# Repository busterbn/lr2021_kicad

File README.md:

# LR2021 868/915 MHz eval module in KiCad

KiCad 10 port of Semtech's LR2021 reference design, the 868/915 MHz evaluation module (e788v01a), converted from the original Altium project.

- `e788v01a/` KiCad project (schematic, board, design rules, symbol and footprint libraries with 3D models)
- `tools/` scripts used for the conversion

Open `e788v01a/LR2021_e788v01a_868_915_eval_module.kicad_pro` in KiCad 10 or newer.

## Verification

- Schematic and PCB connectivity match pin by pin (`tools/check.sh`). The Altium board was used as the reference.
- The board's 107 nets match the Altium PcbDoc, and footprint placement matches Semtech's pick and place file.
- Gerbers plotted from KiCad match Semtech's production Gerbers on all copper, solder mask and paste layers (`tools/gerber_diff.py`). Drill holes match in count and size.

## Notes

- Update PCB from Schematic shows no changes.
- KiCad treats references without a trailing number as unannotated, so 17 Altium designators got a "1" appended (`J7_SWD` is `J7_SWD1`, `868M` is `868M1`, `ANT_HF` is `ANT_HF1`). On the board, their reference fields are hidden and the original names are plain footprint texts at the same place, so the silkscreen is unchanged. If you rename one of these parts, edit that text too.
- The accessories sheet is a sub-sheet of the main sheet. The Altium project was flat, so labels shared by both sheets are global labels.
- `ANT_HF1` and `ANT_LF1` use a 3-pin symbol (1 signal, 2 and 3 GND). The original SMA footprint had pads 1, 2, 2; the second GND pad is now pad 3. The copper is unchanged.
- The Altium logo symbols had a hidden zero-length dummy pin without a pad. It is removed.
- Semtech's Altium design rules are in the `.kicad_pro` board setup, the netclasses and `.kicad_dru`. The RF clearance rules used Altium's auto-generated net names (`NetL*`, `NetC*`, `NetA*`). These nets are in the `RF` netclass.
- 42 vias under U1 and next to the XIAO module are not tented on the bottom side, as in the original.
- DRC still shows warnings that come from the original design: solder mask openings on Q1 that bridge nets, a small VBAT_3V3 copper island on the bottom layer, silkscreen overlaps and a few dangling track stubs.
- ERC shows off-grid warnings (Altium grid) and "power input not driven" errors from Altium pin types.
- `kicad-cli pcb drc --schematic-parity` reports "No corresponding pin" for nets without labels. This looks like a CLI issue.

## Conversion

1. KiCad: File > Import Non-KiCad Project > Altium Project, then save the schematic.
2. `make_hierarchy.py`: turns the two top-level sheets into root sheet plus sub-sheet.
3. `fix_labels.py`, `annotate_power.py`, `fix_pads.py`, `relink.py`, `netmap.py`, `fplib.py`, `export_fps.py`, `rules.py`, `fix_tenting.py`, `fix_refs.py` (then `relink.py`, `netmap.py` and `rules.py` again, since auto-generated net names follow the references), `fix_nopads.py`.
4. KiCad: Update PCB from Schematic, which only adds KiCad 10 footprint metadata and nets for unused pins.
5. After each step, `check.sh` compares schematic and PCB connectivity.

The KiCad Python scripts (`fix_pads.py`, `export_fps.py`, `fix_refs.py`, `fix_nopads.py`) run with KiCad's bundled Python. `fix_tenting.py` and `gerber_diff.py` need `olefile`, `gerbonara`, `pillow` and `numpy`.

## License

The design is Semtech's. Semtech's download contains no license terms, so ask Semtech before you publish or redistribute it. This is not an official Semtech release.

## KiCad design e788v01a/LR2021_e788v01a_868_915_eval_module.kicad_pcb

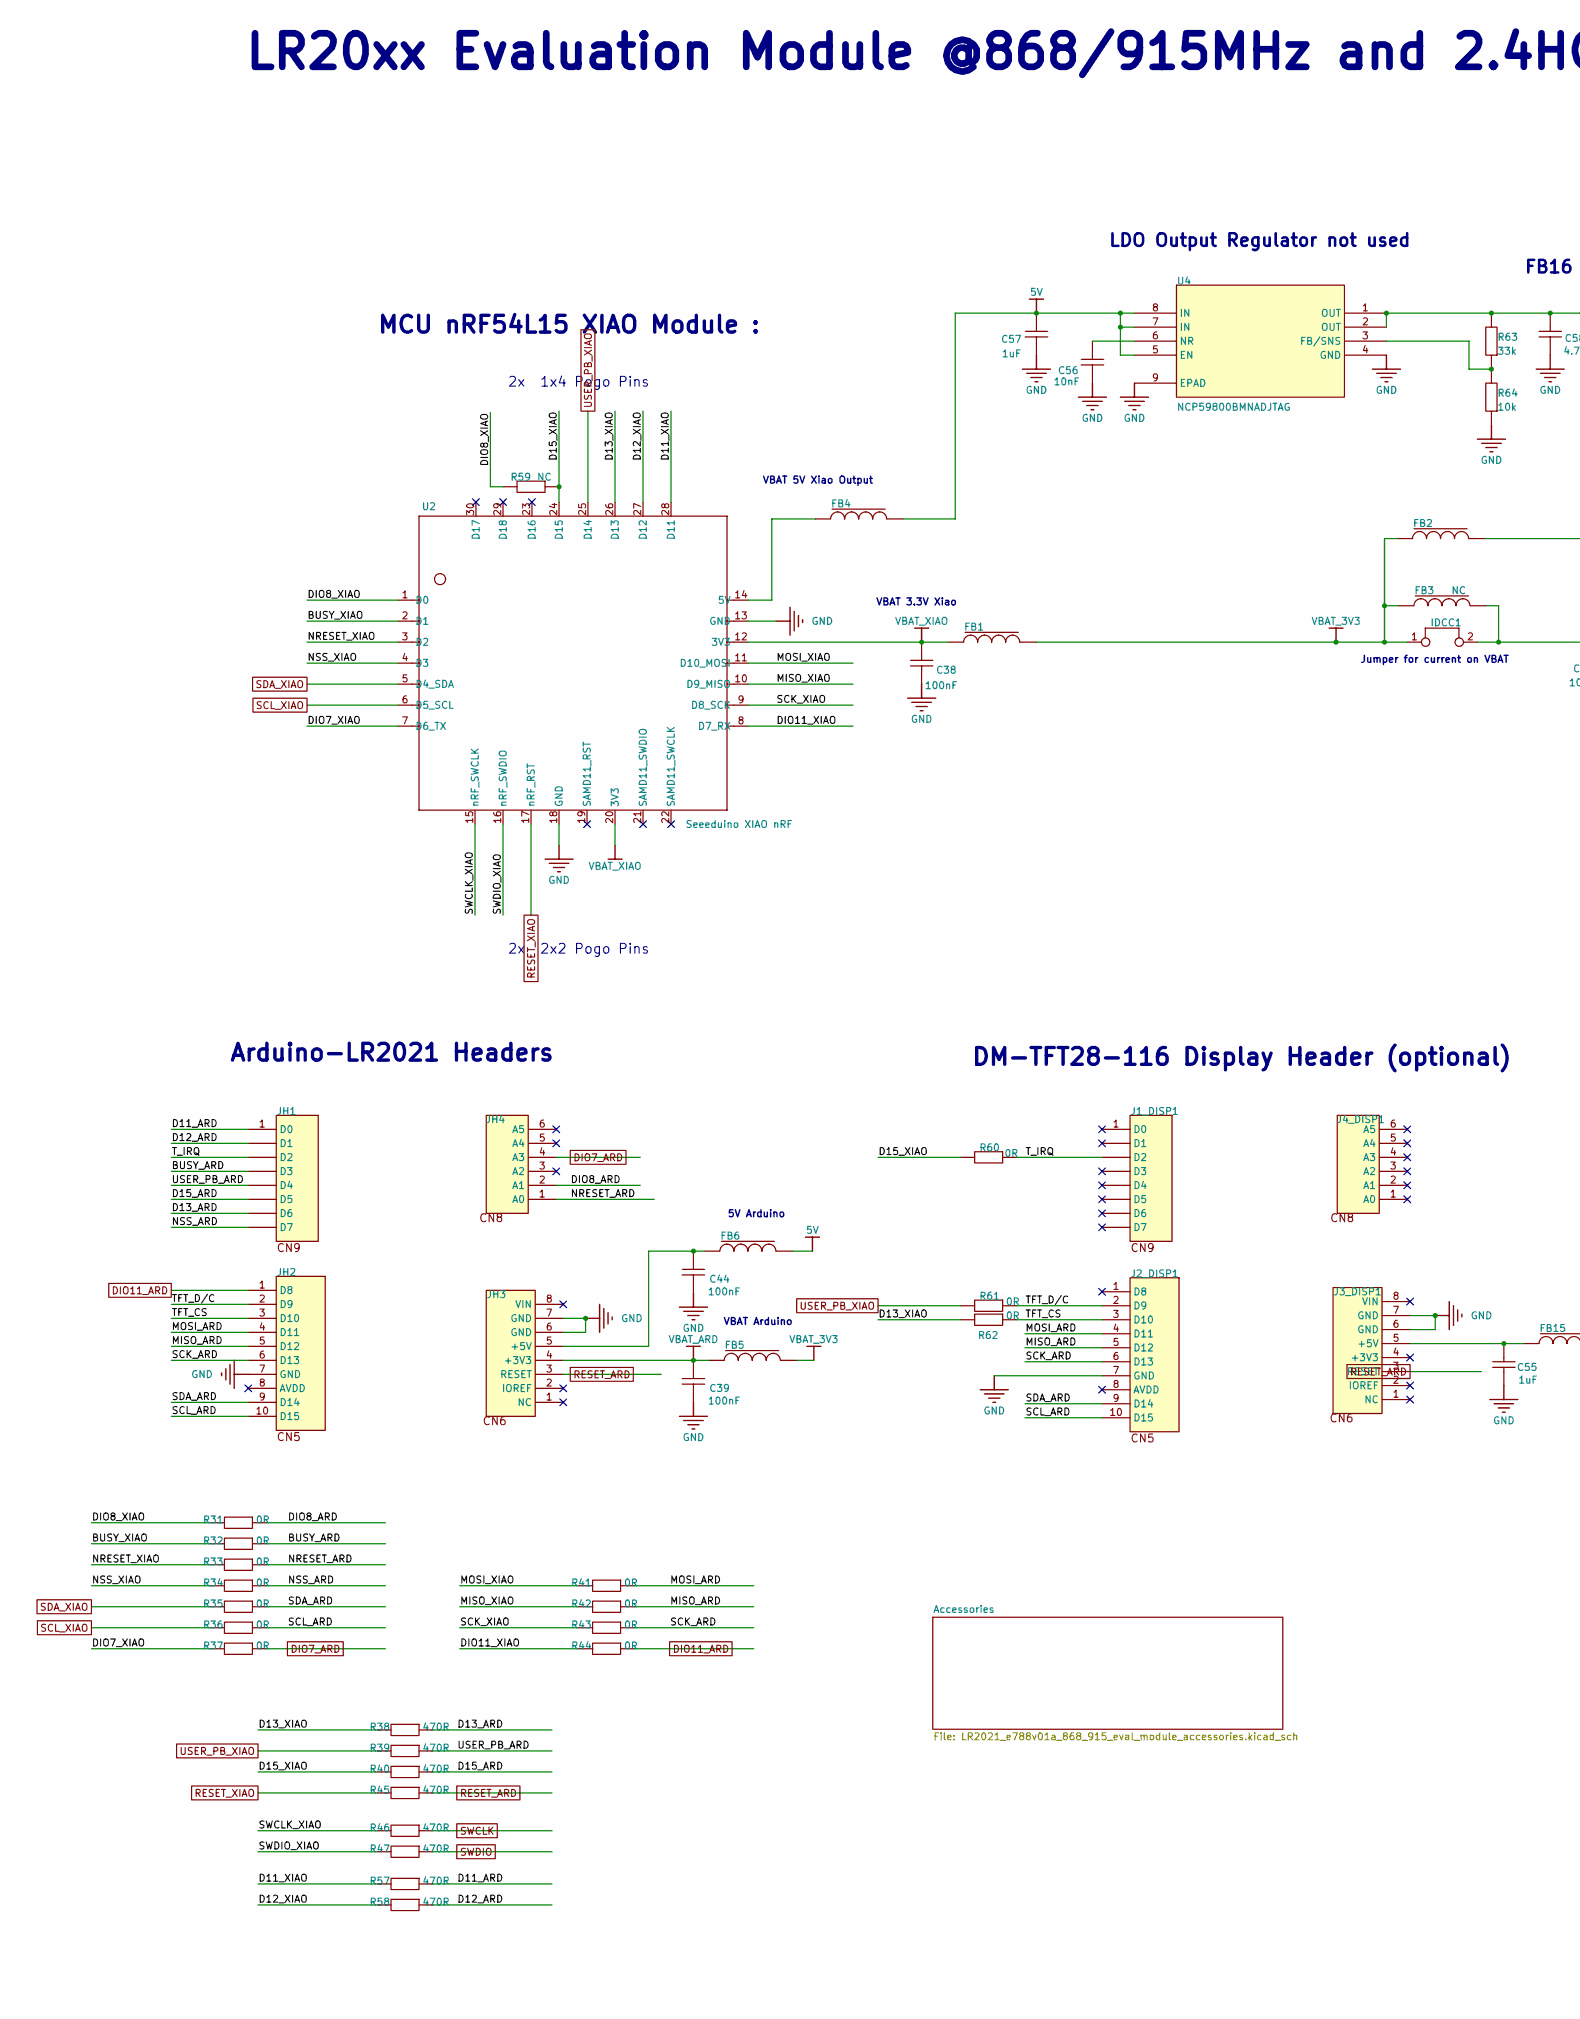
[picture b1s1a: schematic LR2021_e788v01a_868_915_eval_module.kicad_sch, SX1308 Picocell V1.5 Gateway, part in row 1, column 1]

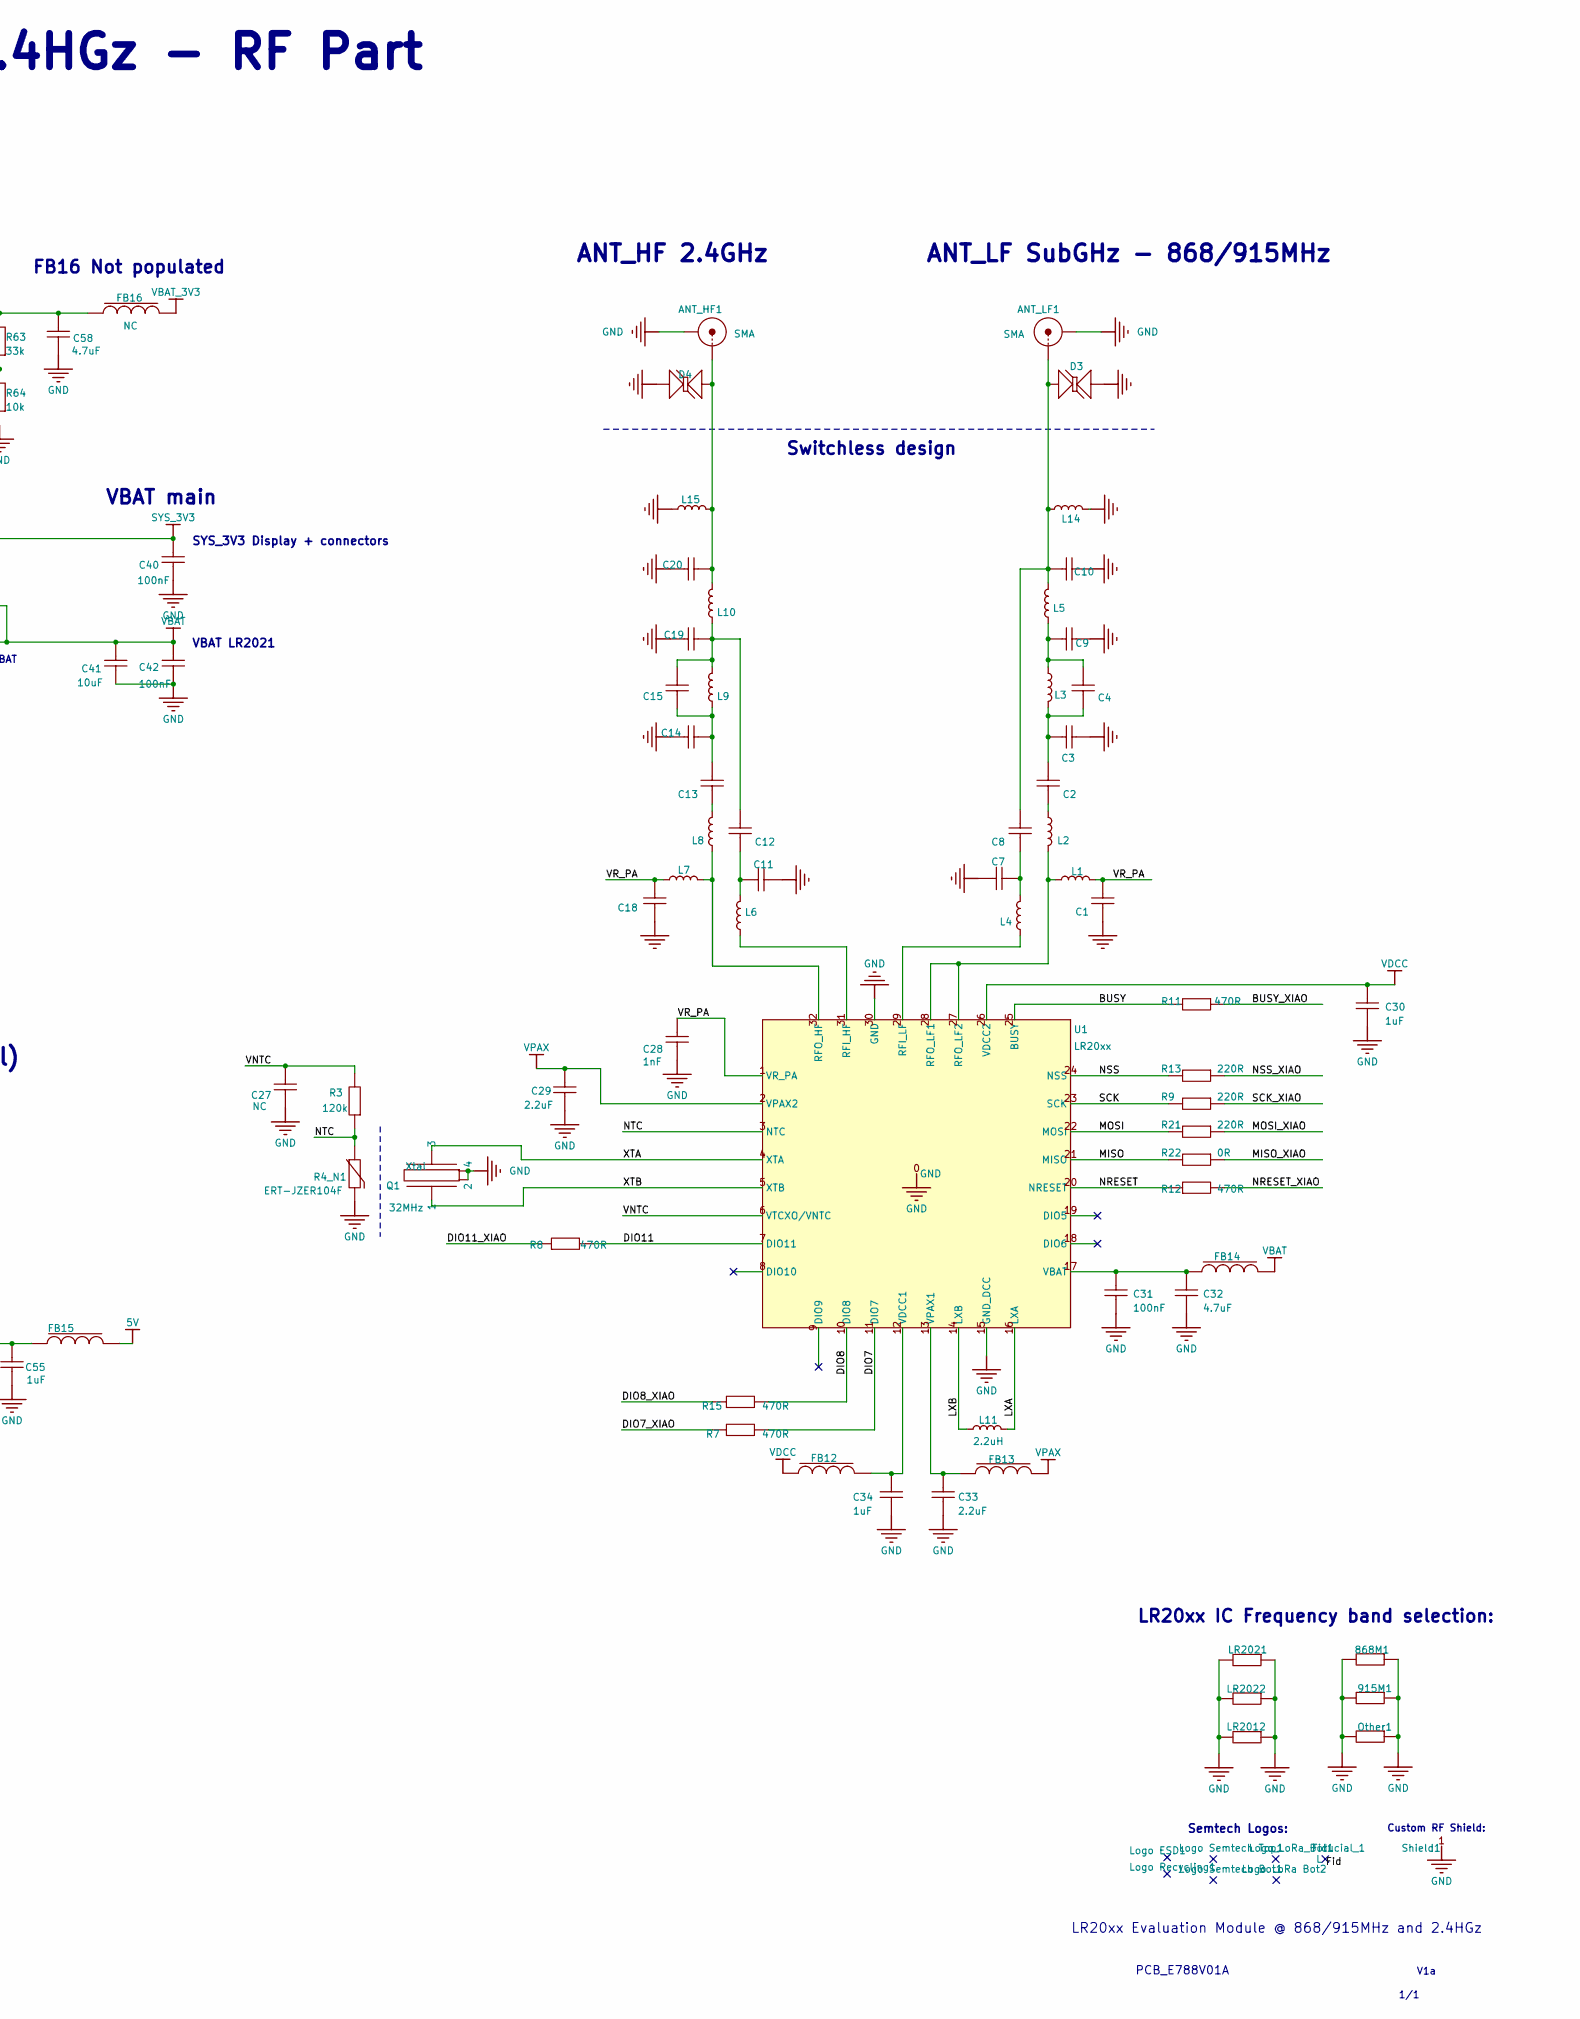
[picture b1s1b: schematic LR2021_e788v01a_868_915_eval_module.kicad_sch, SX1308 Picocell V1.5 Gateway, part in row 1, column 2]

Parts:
868M1, 915M1: Resistor; r_201_smd
ANT_HF1: SMA; SMA_end_launch_1.2mm_6.35mm_female
ANT_LF1: SMA; SMA_end_launch_1.2mm_6.35mm_female
C1, C2, C3, C4, C7, C8, C9, C10, C11, C12, C13, C14, C15, C18, C19, C20, C27, C28, C31, C38, C39, C42, C44, C56: Cap; c_201_smd
C29, C30, C32, C33, C34, C40, C41, C55, C57, C58: Cap; c_402_smd
D3, D4: TVS Diode; SLP0603P2X3F
FB1, FB2, FB3, FB4, FB5, FB6, FB15, FB16: Ferrite beads; Ferrite_402_smd
FB12, FB13, FB14: Ferrite beads; Ferrite_201_smd
Fiducial_1: Fiducial_Mark; fiducial_mark_signal_top Small
IDCC1: Jumper; bridge_254mm
J1_DISP1, J3_DISP1: Header 8; HDR1X8
J2_DISP1: Header 10; HDR1X10
J4_DISP1: Header 6; HDR1X6
JH1: Header 8; HDR1X8 Arduino CN9
JH2: Header 10; HDR1X10 Arduino CN5
JH3: Header 8; HDR1X8 Arduino CN6
JH4: Header 6; HDR1X6 Arduino CN8
L1: Inductor symbol; lqw_402_smd
L2, L3, L5, L6, L7, L8, L9, L10, L14, L15: Inductor symbol; LQW_201_smd
L4: Inductor symbol; LQP_201_smd
L11: Inductor symbol; LQM18P_603_INDUCTOR_SMD
LR2012, LR2021, LR2022: Resistor; r_201_smd
Logo ESD1: Logo symbol; Logo ESD
Logo LoRa Bot2: Logo symbol; Logo LoRa Size4
Logo Recycling1: Logo symbol; Logo Recycling1
Logo Semtech Bot1: Logo symbol; logo_semtech_horiz_size4
Logo Semtech Top1: Logo symbol; logo_semtech_horiz_size3
Logo_LoRa_Bot1: Logo symbol; Logo LoRa Size4
Other1: Resistor; r_201_smd
Q1: Xtal; XTAL_1612
R3, R7, R8, R9, R11, R12, R13, R15, R21, R22, R31, R32, R33, R34, R35, R36, R37, R38, R39, R40, R41, R42, R43, R44, R45, R46, R47, R57, R58, R59, R60, R61, R62, R63, R64: Resistor; r_201_smd
R4_N1: NTC; r_201_smd
Shield1: RF Shield; Custom shield RD LR2021
U1: LR20xx; qfn32l_5x5mm
U2: Seeeduino XIAO nRF; MODULE14P-2.54-21X17.8MM-TEST_nRF54L15
U4: NCP59800BMNADJTAG; DFN8_3X3-0P65_506DB-A_OSI; MANUFACTURER_PART_NUMBER NCP59800BMNADJTAG

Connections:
5V: C57.2, FB4.2, FB6.2, FB15.2, U4.5 (EN), U4.7 (IN), U4.8 (IN); also elsewhere on the board
/BUSY: R11.1, U1.25 (BUSY)
/BUSY_ARD: JH1.4 (D3), R32.2
/BUSY_XIAO: R11.2, R32.1, U2.2 (D1)
/D11_ARD: JH1.1 (D0), R57.2
/D11_XIAO: R57.1, U2.28 (D11)
/D12_ARD: JH1.2 (D1), R58.2
/D12_XIAO: R58.1, U2.27 (D12)
/D13_ARD: JH1.7 (D6), R38.2
/D13_XIAO: R38.1, R62.1, U2.26 (D13)
/D15_ARD: JH1.6 (D5), R40.2
/D15_XIAO: R40.1, R59.2, R60.1, U2.24 (D15)
/DIO7: R7.1, U1.11 (DIO7)
/DIO7_XIAO: R7.2, R37.1, U2.7 (D6_TX)
/DIO8: R15.1, U1.10 (DIO8)
/DIO8_ARD: JH4.2 (A1), R31.2
/DIO8_XIAO: R15.2, R31.1, R59.1, U2.1 (D0)
/DIO11: R8.1, U1.7 (DIO11)
/DIO11_XIAO: R8.2, R44.1, U2.8 (D7_RX)
/Fid: Fiducial_1.0 (L_0)
/LXA: L11.2, U1.16 (LXA)
/LXB: L11.1, U1.14 (LXB)
/MISO: R22.1, U1.21 (MISO)
/MISO_ARD: J2_DISP1.5 (D12), JH2.5 (D12), R42.2
/MISO_XIAO: R22.2, R42.1, U2.10 (D9_MISO)
/MOSI: R21.1, U1.22 (MOSI)
/MOSI_ARD: J2_DISP1.4 (D11), JH2.4 (D11), R41.2
/MOSI_XIAO: R21.2, R41.1, U2.11 (D10_MOSI)
/NRESET: R12.2, U1.20 (NRESET)
/NRESET_ARD: JH4.1 (A0), R33.2
/NRESET_XIAO: R12.1, R33.1, U2.3 (D2)
/NSS: R13.1, U1.24 (NSS)
/NSS_ARD: JH1.8 (D7), R34.2
/NSS_XIAO: R13.2, R34.1, U2.4 (D3)
/NTC: R3.2, R4_N1.2, U1.3 (NTC)
/SCK: R9.1, U1.23 (SCK)
/SCK_ARD: J2_DISP1.6 (D13), JH2.6 (D13), R43.2
/SCK_XIAO: R9.2, R43.1, U2.9 (D8_SCK)
/SCL_ARD: J2_DISP1.10 (D15), JH2.10 (D15), R36.2
/SDA_ARD: J2_DISP1.9 (D14), JH2.9 (D14), R35.2
/SWCLK_XIAO: R46.1, U2.15 (nRF_SWCLK)
/SWDIO_XIAO: R47.1, U2.16 (nRF_SWDIO)
/TFT_CS: J2_DISP1.3 (D10), JH2.3 (D10), R62.2
/TFT_D/C: J2_DISP1.2 (D9), JH2.2 (D9), R61.2
/T_IRQ: J1_DISP1.3 (D2_3), JH1.3 (D2), R60.2
/USER_PB_ARD: JH1.5 (D4), R39.2
/VNTC: C27.2, R3.1, U1.6 (VTCXO/VNTC)
/VR_PA: C1.2, C18.2, C28.2, L1.1, L7.1, U1.1 (VR_PA)
/XTA: Q1.3, U1.4 (XTA)
/XTB: Q1.1, U1.5 (XTB)
DIO7_ARD: JH4.4 (A3), R37.2; also elsewhere on the board
DIO11_ARD: JH2.1 (D8), R44.2; also elsewhere on the board
GND: 868M1.1, 868M1.2, 915M1.1, 915M1.2, ANT_HF1.2 (GND), ANT_HF1.3 (GND), ANT_LF1.2 (GND), ANT_LF1.3 (GND), C1.1, C3.1, C7.1, C9.1, C10.1, C11.1, C14.1, C18.1, C19.1, C20.1, C27.1, C28.1, C29.1, C30.1, C31.1, C32.1, C33.1, C34.1, C38.1, C39.1, C40.1, C41.1, C42.1, C44.1, C55.1, C56.1, C57.1, C58.1, D3.1 (A), D4.1 (A), J2_DISP1.7 (GND), J3_DISP1.6 (GND), J3_DISP1.7 (GND), JH2.7 (GND), JH3.6 (GND), JH3.7 (GND), L14.2, L15.1, LR2012.1, LR2012.2, LR2021.1, LR2021.2, LR2022.1, LR2022.2, Other1.1, Other1.2, Q1.2, Q1.4, R4_N1.1, R64.2, Shield1.1 (1_1), U1.0 (GND), U1.15 (GND_DCC), U1.30 (GND), U2.13 (GND), U2.18 (GND), U4.4 (GND), U4.9 (EPAD); also elsewhere on the board
unnamed: ANT_HF1.1 (Signal), C20.2, D4.2 (K), L10.2, L15.2
unnamed: ANT_LF1.1 (Signal), C8.2, C10.2, D3.2 (K), L5.2, L14.1
unnamed: C2.1, L2.2
unnamed: C2.2, C3.2, C4.1, L3.1
unnamed: C4.2, C9.2, L3.2, L5.1
unnamed: C7.2, C8.1, L4.2
unnamed: C11.2, C12.1, L6.1
unnamed: C12.2, C15.2, C19.2, L9.2, L10.1
unnamed: C13.1, L8.2
unnamed: C13.2, C14.2, C15.1, L9.1
unnamed: C58.2, FB16.1, R63.1, U4.1 (OUT), U4.2 (OUT)
unnamed: C55.2, FB15.1, J3_DISP1.5 (+5V)
unnamed: C44.2, FB6.1, JH3.5 (+5V)
unnamed: L6.2, U1.31 (RFI_HF)
unnamed: L4.1, U1.29 (RFI_LF)
unnamed: L7.2, L8.1, U1.32 (RFO_HF)
unnamed: L1.2, L2.1, U1.27 (RFO_LF2), U1.28 (RFO_LF1)
unnamed: C31.2, C32.2, FB14.1, U1.17 (VBAT)
unnamed: C34.2, FB12.2, U1.12 (VDCC1)
unnamed: C33.2, FB13.1, U1.13 (VPAX1)
unnamed: FB4.1, U2.14 (5V)
unnamed: R63.2, R64.1, U4.3 (FB/SNS)
unnamed: C56.2, U4.6 (NR)
RESET_ARD: J3_DISP1.3 (RESET), JH3.3 (RESET), R45.2; also elsewhere on the board
RESET_XIAO: R45.1, U2.17 (nRF_RST); also elsewhere on the board
SCL_XIAO: R36.1, U2.6 (D5_SCL); also elsewhere on the board
SDA_XIAO: R35.1, U2.5 (D4_SDA); also elsewhere on the board
SWCLK: R46.2; also elsewhere on the board
SWDIO: R47.2; also elsewhere on the board
SYS_3V3: C40.2, FB2.2; also elsewhere on the board
USER_PB_XIAO: R39.1, R61.1, U2.25 (D14); also elsewhere on the board
VBAT: C41.2, C42.2, FB3.2, FB14.2, IDCC1.2
VBAT_3V3: FB1.2, FB2.1, FB3.1, FB5.2, FB16.2, IDCC1.1
VBAT_ARD: C39.2, FB5.1, JH3.4 (+3V3)
VBAT_XIAO: C38.2, FB1.1, U2.12 (3V3), U2.20 (3V3)
VDCC: C30.2, FB12.1, U1.26 (VDCC2)
VPAX: C29.2, FB13.2, U1.2 (VPAX2)

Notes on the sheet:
VBAT Arduino
MCU nRF54L15 XIAO Module :
LR20xx IC Frequency band selection:
SYS_3V3 Display + connectors
PCB_E788V01A
VBAT main
LR20xx Evaluation Module @ 868/915MHz and 2.4HGz
5V Arduino
V1a
ANT_HF 2.4GHz
ANT_LF SubGHz - 868/915MHz
LDO Output Regulator not used
Jumper for current on VBAT
VBAT 3.3V Xiao
LR20xx Evaluation Module @868/915MHz and 2.4HGz - RF Part
VBAT LR2021
FB16 Not populated
Arduino-LR2021 Headers
VBAT 5V Xiao Output
Switchless design
1/1
2x 2x2 Pogo Pins
Custom RF Shield:
2x 1x4 Pogo Pins
DM-TFT28-116 Display Header (optional)
Semtech Logos:

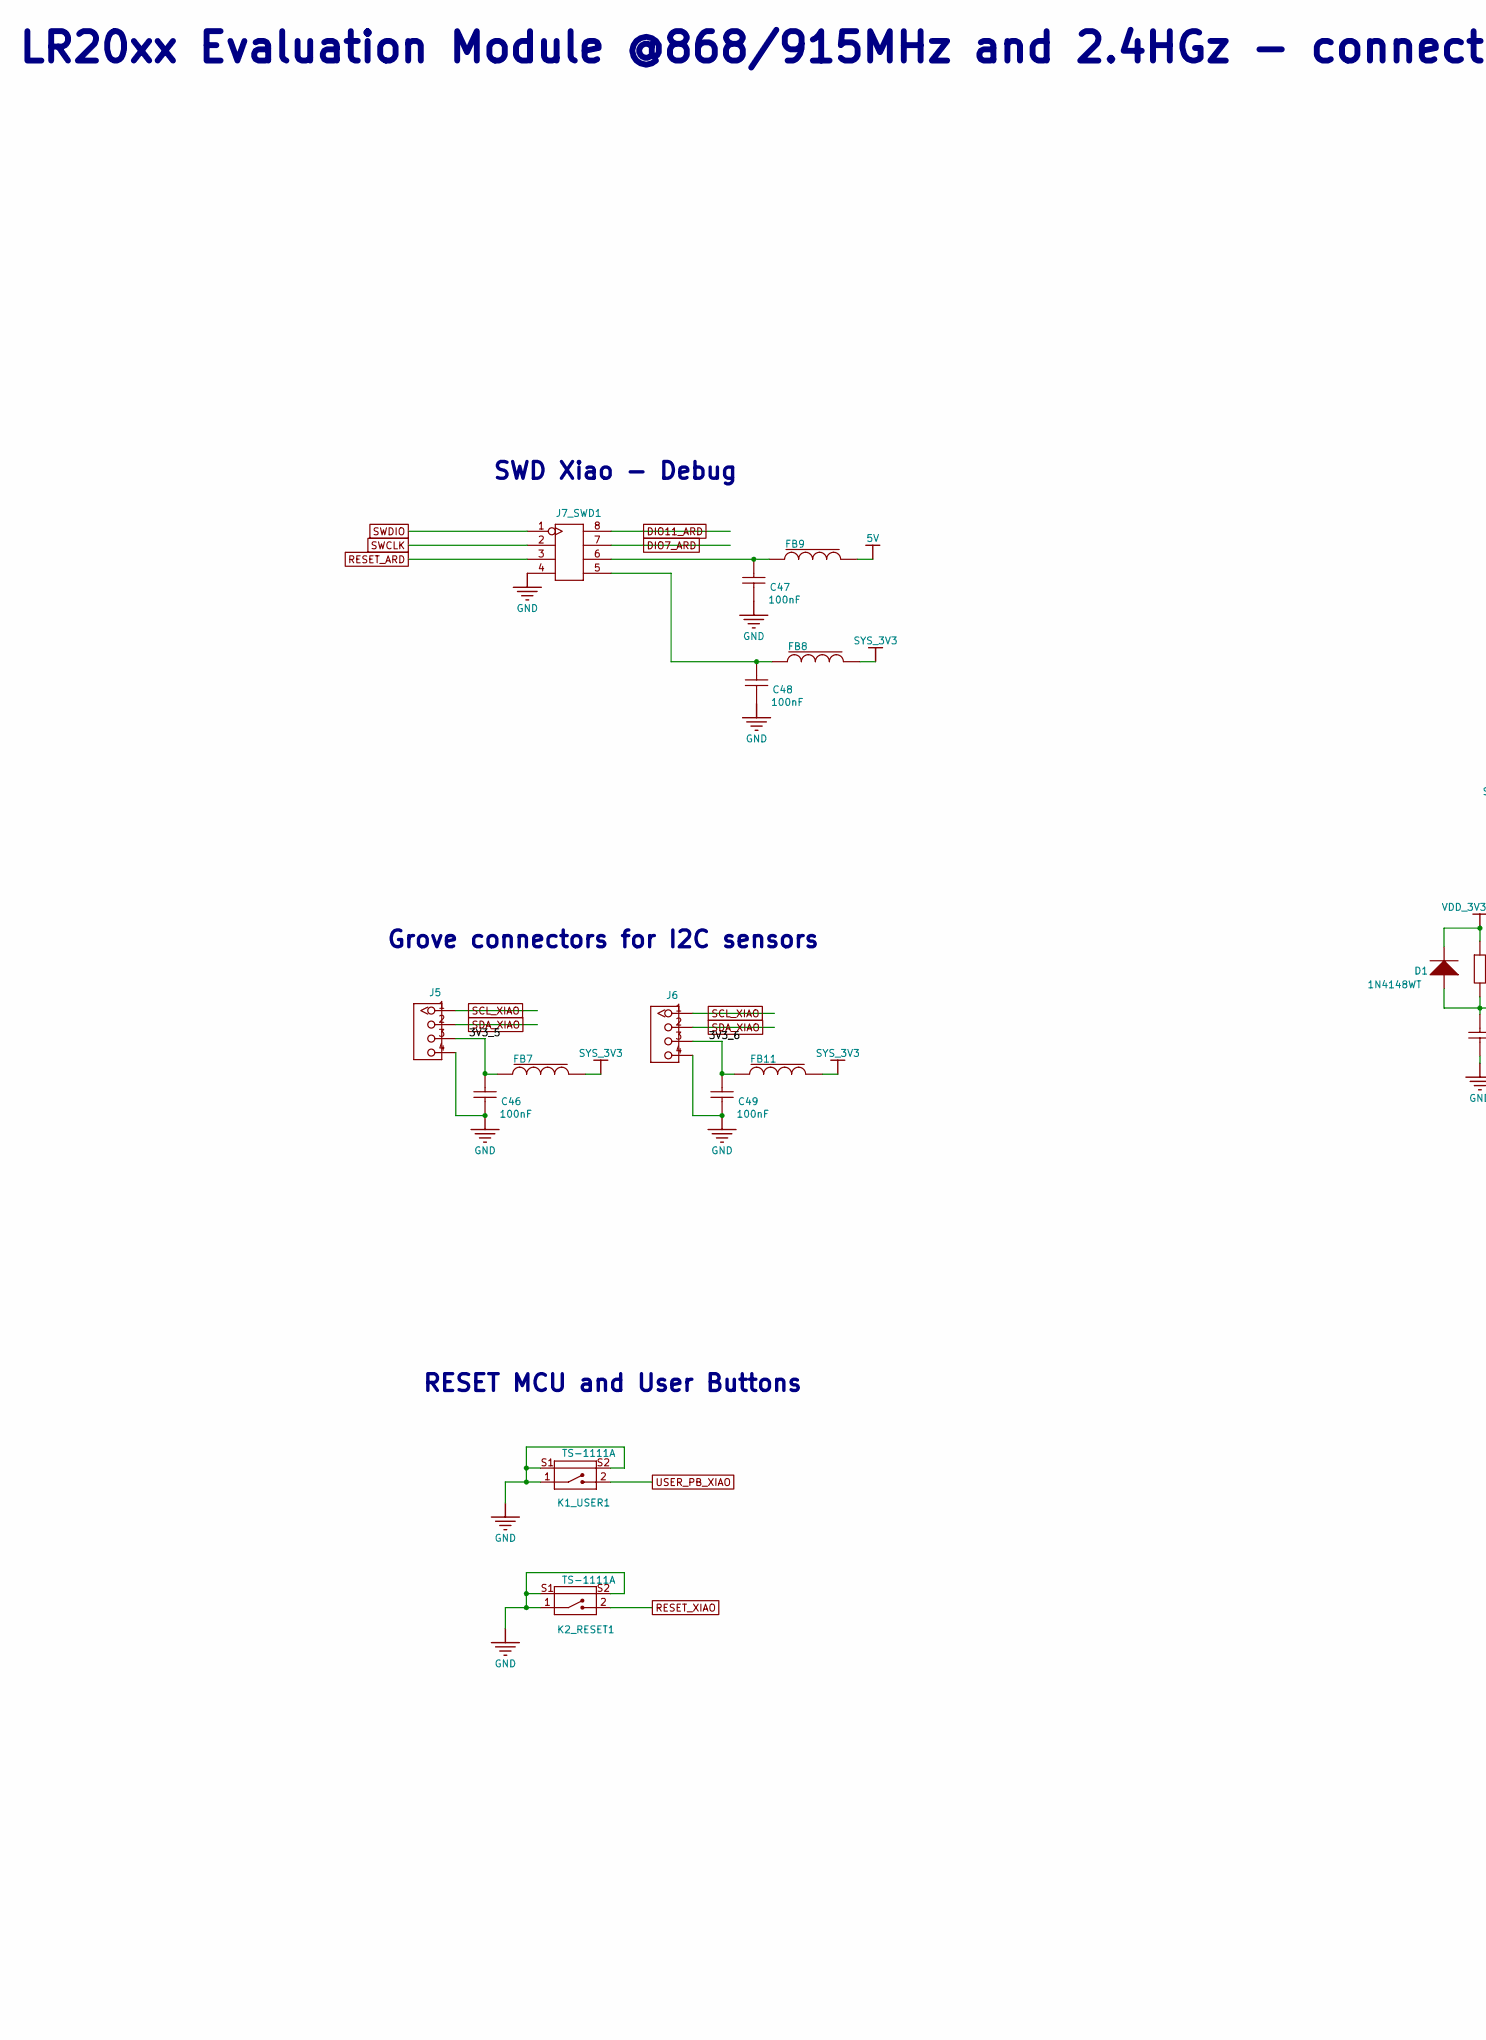
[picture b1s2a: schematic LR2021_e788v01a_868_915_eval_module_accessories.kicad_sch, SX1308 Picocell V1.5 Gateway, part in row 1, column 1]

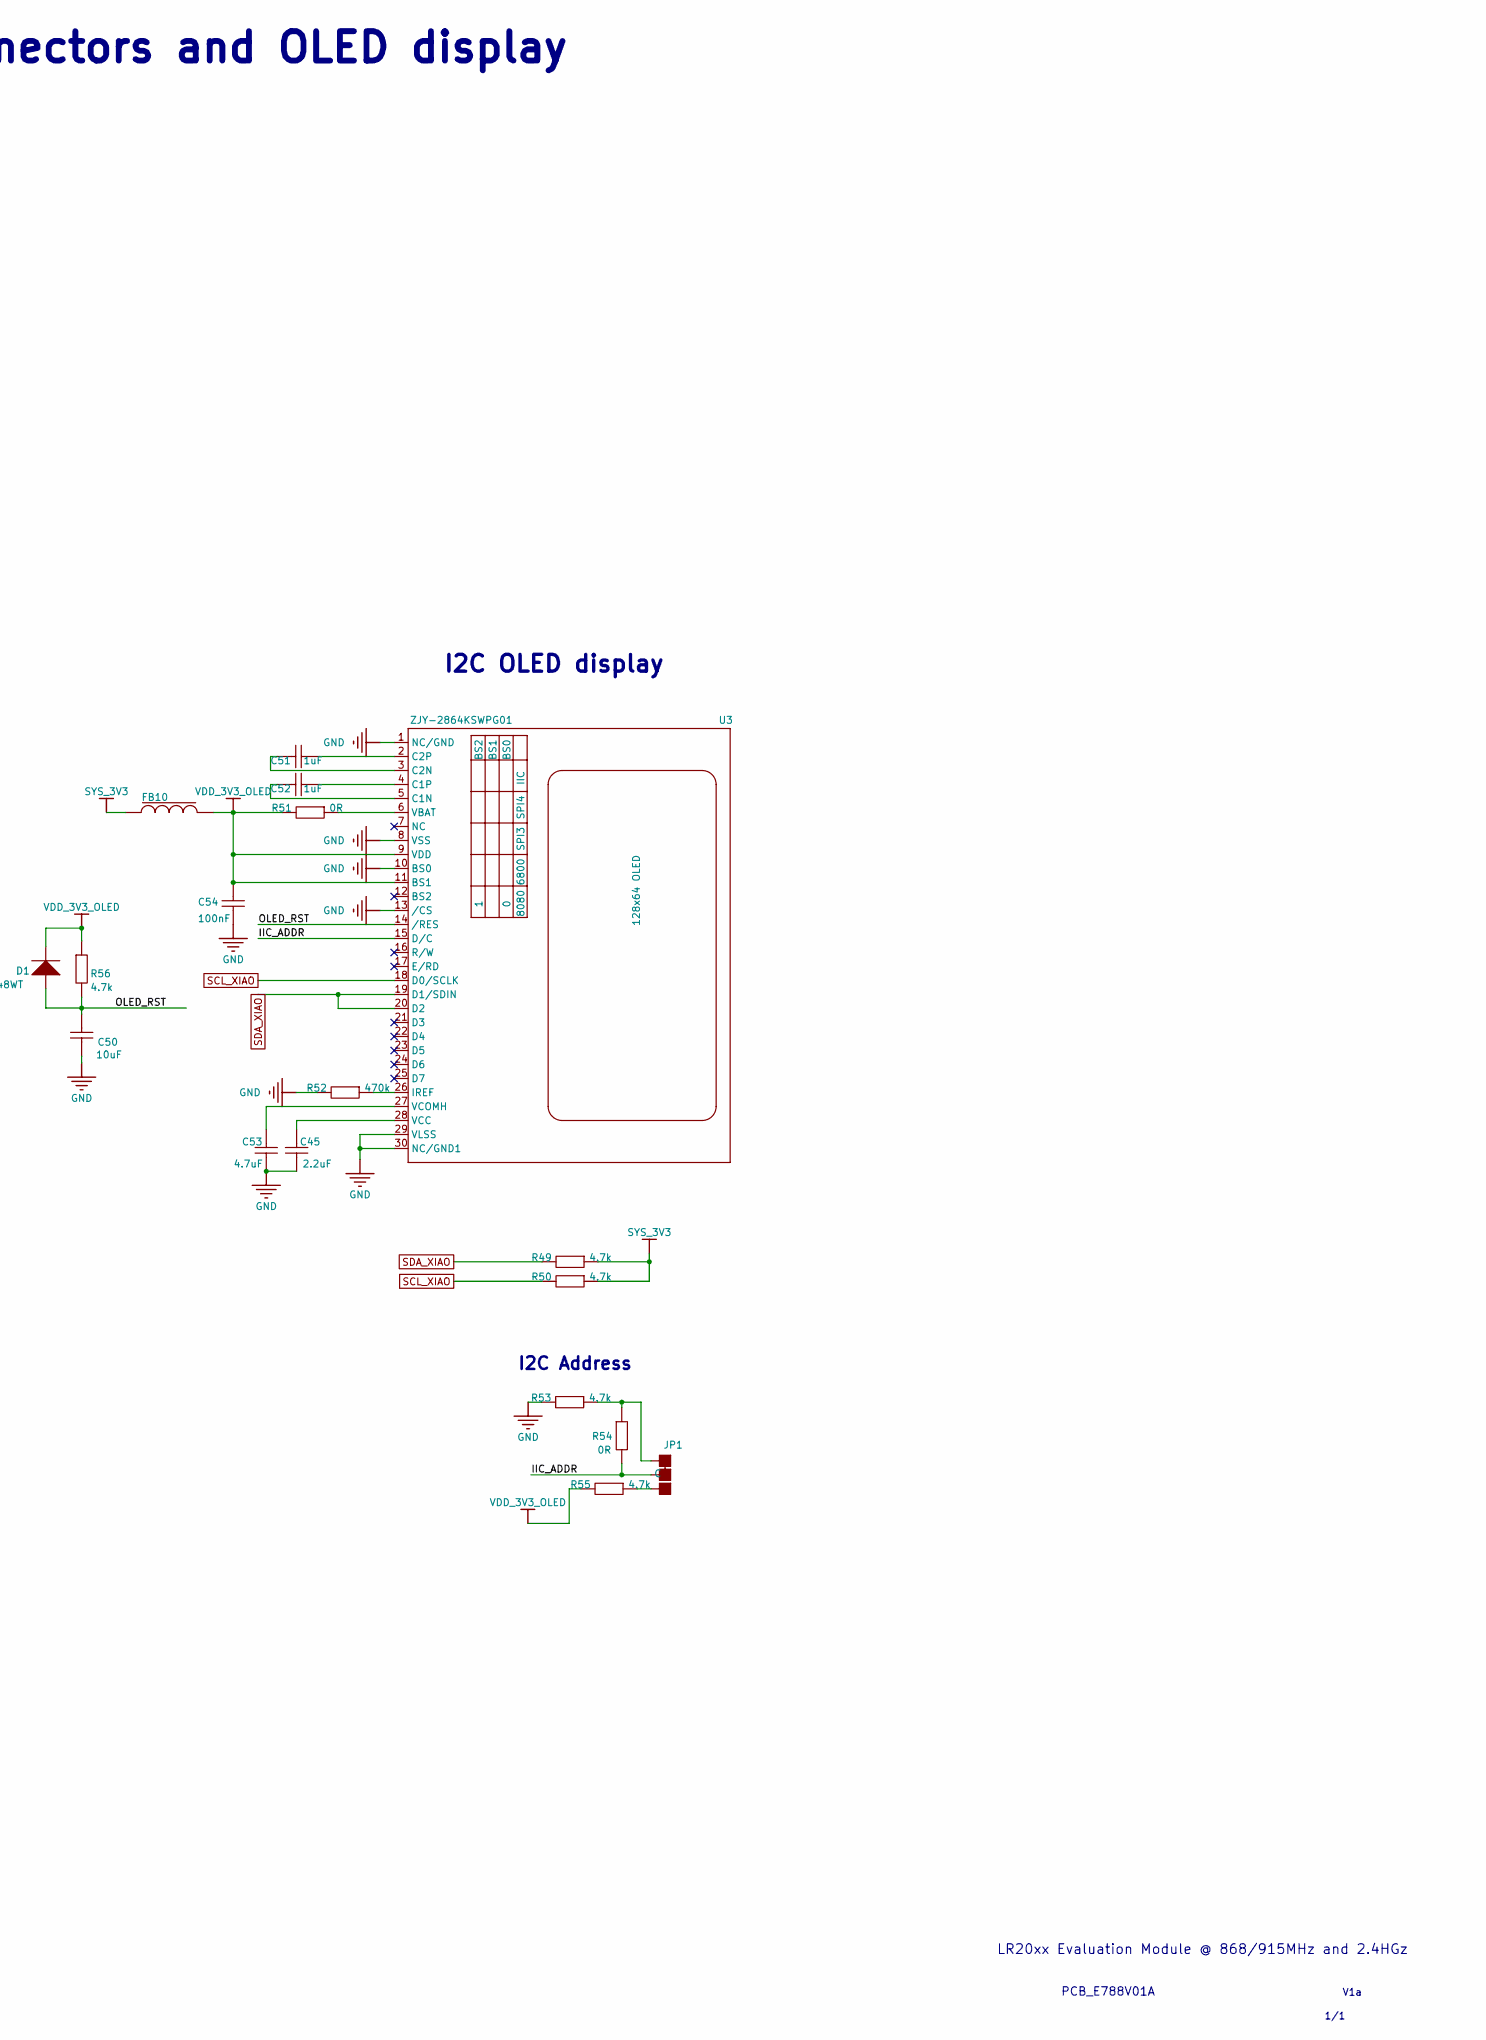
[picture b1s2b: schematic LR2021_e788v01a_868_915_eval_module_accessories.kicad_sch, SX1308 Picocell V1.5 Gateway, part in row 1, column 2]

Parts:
C45, C50, C51, C52, C53: Cap; c_402_smd
C46, C47, C48, C49, C54: Cap; c_201_smd
D1: 1N4148WT; SOD-523
FB7, FB8, FB9, FB11: Ferrite beads; Ferrite_201_smd
FB10: Ferrite beads; Ferrite_402_smd
J5, J6: GROVE-CONNECTOR-DIP-320110034; HW4-2.0-00D
J7_SWD1: HEADER-2X4P-2.54-SMD; H2X4-SMD-2.54
JP1: JP-3P-SHORT; 3P-SMD-SHORT
K1_USER1, K2_RESET1: TS-1111A; SW4-SMD-4.5X3.8X1.8MM-90D
R49, R50: Resistor; r_201_smd
R51, R52, R53, R54, R55, R56: Resistor; r_402_smd
U3: ZJY-2864KSWPG01; OLED30P-0.7-24.74X16.9MM

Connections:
5V: FB9.2; also elsewhere on the board
/Accessories/3V3_5: C46.2, FB7.1, J5.3
/Accessories/3V3_6: C49.2, FB11.1, J6.3
/Accessories/IIC_ADDR: JP1.MM (C), R54.1, U3.15 (D/C)
/Accessories/OLED_RST: C50.2, D1.1 (A), R56.1, U3.14 (/RES)
DIO7_ARD: J7_SWD1.7; also elsewhere on the board
DIO11_ARD: J7_SWD1.8; also elsewhere on the board
GND: C45.2, C46.1, C47.1, C48.1, C49.1, C50.1, C53.2, C54.2, J5.4, J6.4, J7_SWD1.4, K1_USER1.1, K1_USER1.S1, K1_USER1.S2, K2_RESET1.1, K2_RESET1.S1, K2_RESET1.S2, R52.1, R53.1, U3.1 (NC/GND), U3.8 (VSS), U3.10 (BS0), U3.13 (/CS), U3.29 (VLSS), U3.30 (NC/GND1); also elsewhere on the board
unnamed: C47.2, FB9.1, J7_SWD1.6
unnamed: C48.2, FB8.1, J7_SWD1.5
unnamed: JP1.11 (L), R53.2, R54.2
unnamed: JP1.00 (R), R55.2
unnamed: C52.2, U3.5 (C1N)
unnamed: C52.1, U3.4 (C1P)
unnamed: C51.2, U3.3 (C2N)
unnamed: C51.1, U3.2 (C2P)
unnamed: R52.2, U3.26 (IREF)
unnamed: R51.2, U3.6 (VBAT)
unnamed: C45.1, U3.28 (VCC)
unnamed: C53.1, U3.27 (VCOMH)
RESET_ARD: J7_SWD1.3; also elsewhere on the board
RESET_XIAO: K2_RESET1.2; also elsewhere on the board
SCL_XIAO: J5.1, J6.1, R50.1, U3.18 (D0/SCLK); also elsewhere on the board
SDA_XIAO: J5.2, J6.2, R49.1, U3.19 (D1/SDIN), U3.20 (D2); also elsewhere on the board
SWCLK: J7_SWD1.2; also elsewhere on the board
SWDIO: J7_SWD1.1; also elsewhere on the board
SYS_3V3: FB7.2, FB8.2, FB10.1, FB11.2, R49.2, R50.2; also elsewhere on the board
USER_PB_XIAO: K1_USER1.2; also elsewhere on the board
VDD_3V3_OLED: C54.1, D1.2 (K), FB10.2, R51.1, R55.1, R56.2, U3.9 (VDD), U3.11 (BS1)

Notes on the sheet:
1/1
LR20xx Evaluation Module @868/915MHz and 2.4HGz - connectors and OLED display
I2C Address
V1a
LR20xx Evaluation Module @ 868/915MHz and 2.4HGz
RESET MCU and User Buttons
Grove connectors for I2C sensors
I2C OLED display
PCB_E788V01A
SWD Xiao - Debug

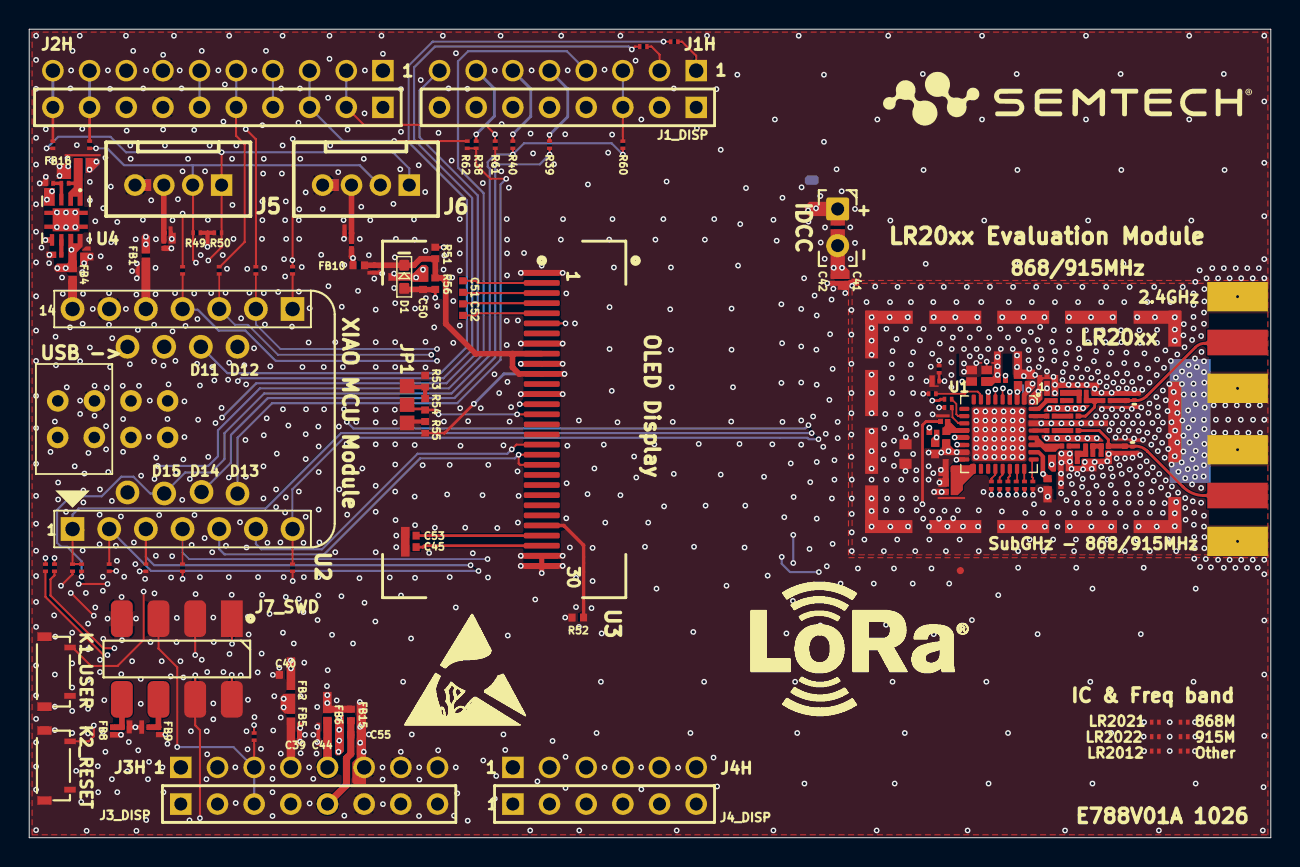
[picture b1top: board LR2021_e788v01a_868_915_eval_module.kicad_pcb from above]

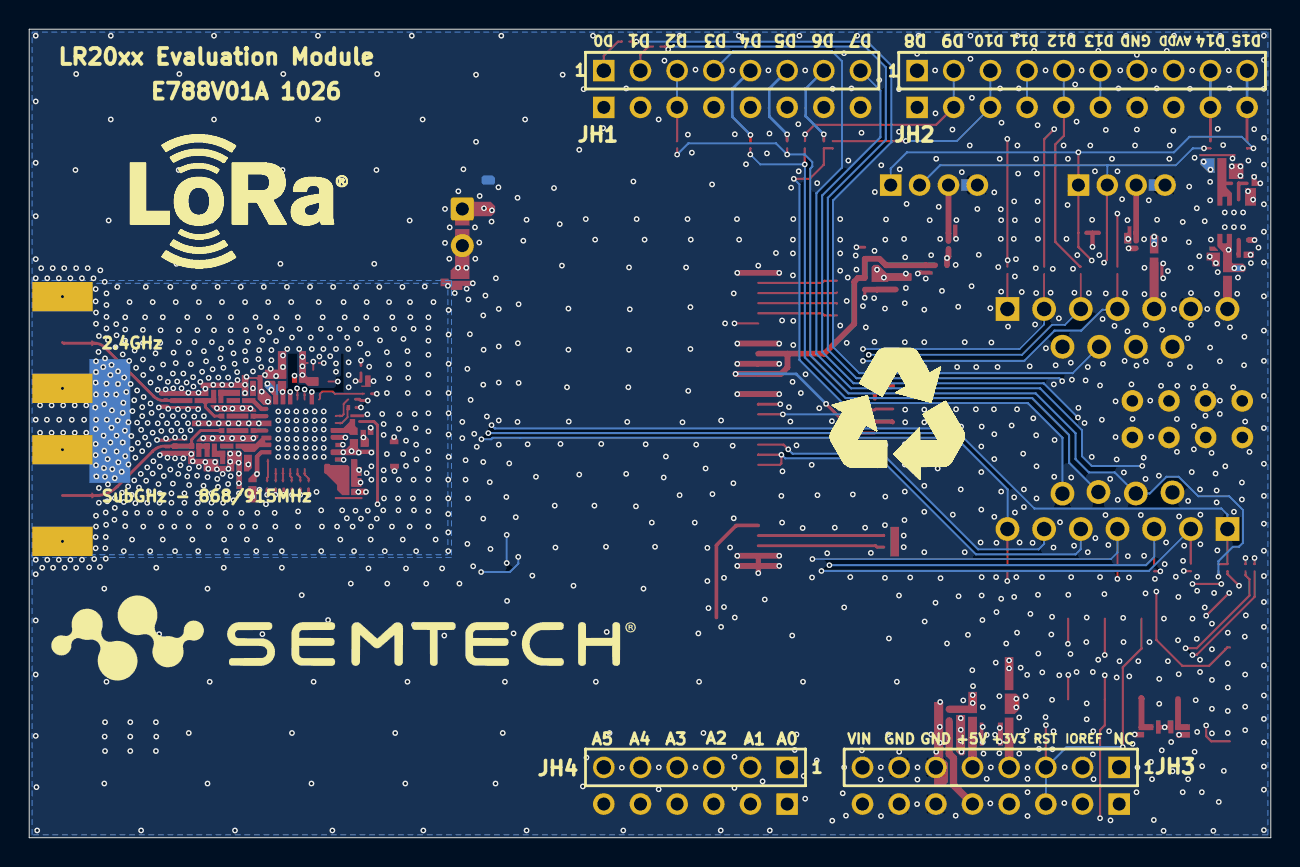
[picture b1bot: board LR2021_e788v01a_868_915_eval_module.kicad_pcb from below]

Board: 4 copper layers, 86.0 x 56.0 mm, 156 parts (7 on the bottom side), 106 nets.

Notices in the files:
parts and their libraries:
COPYRIGHT: Copyright (C) 2025 Ultra Librarian. All rights reserved.
